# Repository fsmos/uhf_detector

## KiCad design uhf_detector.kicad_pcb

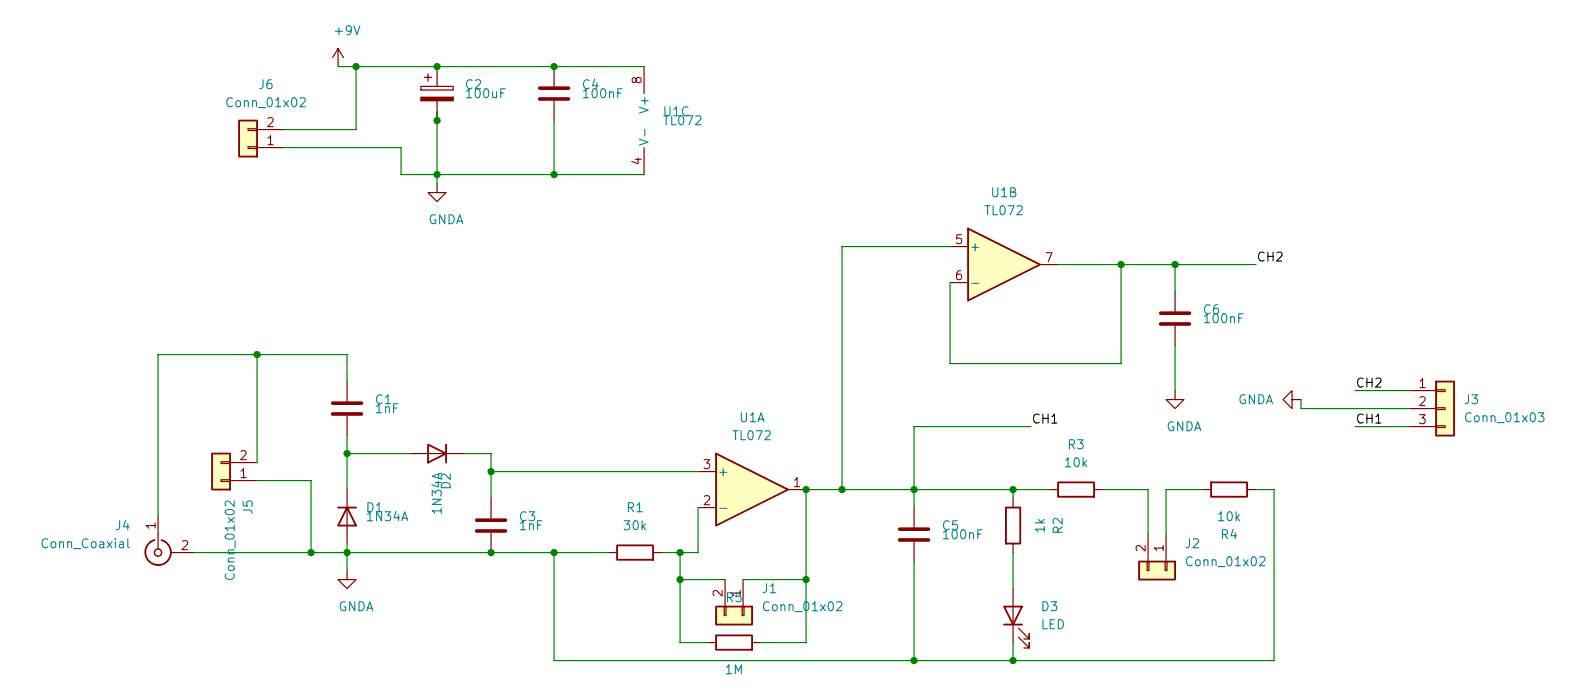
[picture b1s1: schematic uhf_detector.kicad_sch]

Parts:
C1, C3: 1nF; C_0805_2012Metric
C2: 100uF; CP_Radial_D10.0mm_P5.00mm
C4, C5, C6: 100nF; C_0805_2012Metric
D1, D2: 1N34A; D_DO-15_P15.24mm_Horizontal
D3: LED; LED_D5.0mm
J1, J2, J5, J6: Conn_01x02; PinHeader_1x02_P2.54mm_Vertical
J3: Conn_01x03; PinHeader_1x03_P2.54mm_Vertical
J4: Conn_Coaxial; SMA_Amphenol_132291_Vertical
R1: 30k; R_0805_2012Metric
R2: 1k; R_0805_2012Metric
R3, R4: 10k; R_0805_2012Metric
R5: 1M; R_0805_2012Metric
U1: TL072; SO-8_3.9x4.9mm_P1.27mm

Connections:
+9V: C2.1, C4.1, J6.2, U1.8 (V+)
/CH1: C5.1, J1.1, J3.3, R2.1, R3.1, R5.2, U1.1, U1.5 (+)
/CH2: C6.1, J3.1, U1.6 (-), U1.7
GNDA: C2.2, C3.2, C4.2, C5.2, C6.2, D1.2 (A), D3.1 (K), J3.2, J4.2 (Ext), J5.1, J6.1, R1.1, R4.1, U1.4 (V-)
unnamed: C1.1, J4.1 (In), J5.2
unnamed: C1.2, D1.1 (K), D2.2 (A)
unnamed: C3.1, D2.1 (K), U1.3 (+)
unnamed: D3.2 (A), R2.2
unnamed: J1.2, R1.2, R5.1, U1.2 (-)
unnamed: J2.1, R4.2
unnamed: J2.2, R3.2

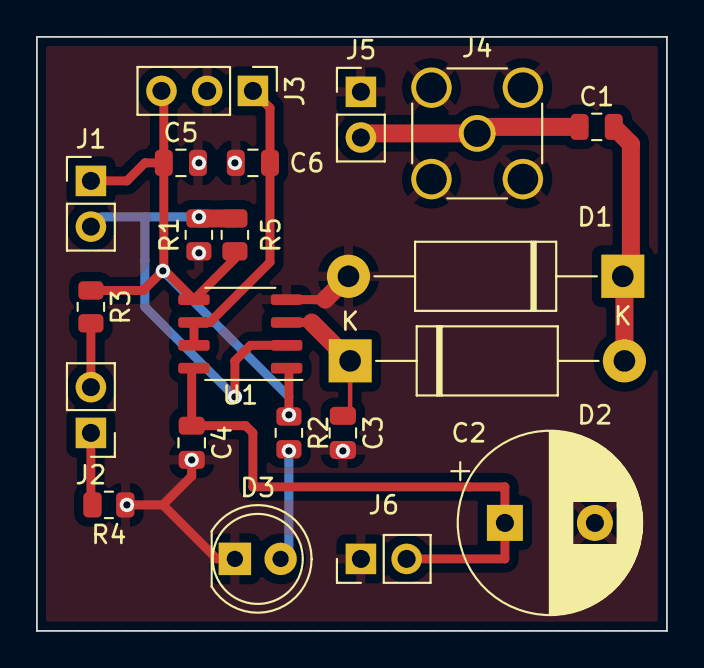
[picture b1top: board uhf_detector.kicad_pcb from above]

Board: 2 copper layers, 35.0 x 33.0 mm, 21 parts (0 on the bottom side), 11 nets.
